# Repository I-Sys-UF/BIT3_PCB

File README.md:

# BIT3_PCB

KiCad 7.0.x にて設計

# BIT とは

**B**eginning **I**.Sys **T**racer のイニシャルで、新入生教育用のライントレーサの筐体です  
先代の BIT2 の設計を踏襲しつつ、マイコンを RP2040 搭載の秋月製 AE-RP2040 に置き換えました。ギアボックス等は流用できるようにしています

# 部品表

## 主要部品

| 部品番号 | 部品名 | 秋月 |
|:----|:----|:----|
| R1 - R5, R11 | 100 Ω | [125101](https://akizukidenshi.com/catalog/g/g125101/) |
| R6 - R10 | 4.7k Ω | [125273](https://akizukidenshi.com/catalog/g/g125273/) |
| R12 - R16 | 510 Ω | [125511](https://akizukidenshi.com/catalog/g/g125511/) |
| R17 - R21 | 1k Ω | [125102](https://akizukidenshi.com/catalog/g/g125102/) |
| C1 - C3 | 0.1 uF | [110147](https://akizukidenshi.com/catalog/g/g110147/) |
| D1 - D5 | 5mm LED | [113172](https://akizukidenshi.com/catalog/g/g113172/) |
| D6 | 1N4148 | [100941](https://akizukidenshi.com/catalog/g/g100941/) |
| U1 | AE-RP2040 | [117542](https://akizukidenshi.com/catalog/g/g117542/) |
| U2 - U6 | LBR-127HLD | [104500](https://akizukidenshi.com/catalog/g/g104500/) |
| U7 | MCP3008 | [109485](https://akizukidenshi.com/catalog/g/g109485/) |
| U7 | IC ソケット | [100007](https://akizukidenshi.com/catalog/g/g100007/) |
| U8 | AE-DRV8835 | [109848](https://akizukidenshi.com/catalog/g/g109848/) |
| U9 | NJM7805FA | [108678](https://akizukidenshi.com/catalog/g/g108678/) |
| Q1 | MOSFET | [107597](https://akizukidenshi.com/catalog/g/g107597/) |
| F1 | リセッタブルヒューズ | [112628](https://akizukidenshi.com/catalog/g/g112628/) |
| SW1 | 電源スイッチ | [100300](https://akizukidenshi.com/catalog/g/g100300/) |
| EXEC, MODE | タクタイルスイッチ | [103647](https://akizukidenshi.com/catalog/g/g103647/) |
| J1 | 2 列ピンヘッダ | [100080](https://akizukidenshi.com/catalog/g/g100080/) |
| J2 | バッテリ接続用ケーブル・コネクタ | 省略 |
| J3, U1 | 1 列ピンソケット | [105779](https://akizukidenshi.com/catalog/g/g105779/) |
| J5, J6 | 7 セグメント LED  | [110344](https://akizukidenshi.com/catalog/g/g110344/) |

## その他の部品

| 部品名 | 商品名 | リンク |
|:----|:----|:----|
| 前輪 | タミヤ　ボールキャスター | <https://tamiyashop.jp/shop/g/g70144> |
| 動力 | タミヤ　ダブルギヤボックス（左右独立4速タイプ） | <https://tamiyashop.jp/shop/g/g70168> |
| 後輪 | タミヤ　スリムタイヤセット | <https://tamiyashop.jp/shop/g/g70193> |
| XBee | XBee S2C ワイヤアンテナ型 | <https://www.switch-science.com/products/4089> |
| XBee 用変換基板 | XBeeエクスプローラ5Vマイコン用 | <https://www.switch-science.com/products/1166> |
| XBee 用 USB アダプタ | XBeeエクスプローラUSBドングル | <https://www.switch-science.com/products/1790> |

# 回路図

# 基板デザイン

# 更新履歴

- `v1.0`
  - 初回リリース
- `v1.1`
  - ADC にバッテリ電圧が直接入力される問題を修正
- `v1.2`
  - 接続されていない GND ベタが存在する問題を修正
- `v1.3`
  - モータ・ドライバに電源が供給されていない問題を修正
- `v1.4`
  - ADC IC MCP3008 にパスコンを追加
- `v1.5` 
  - 前輪と部品が微妙に干渉する問題を修正
- `v1.6`
  - 逆接防止ダイオードの追加、バッテリ入力の接続の変更、一部部品の変更（基板には影響なし）
- `v1.7`
  - フォトセンサを変更
- `v2.0`
  - XBee 接続用のコネクタを追加
- `v2.1`
  - BACK を EXEC に変更
- `v2.2`
  -  フォトセンサ駆動用トランジスタを変更
- `V2.3`
  - 7 セグメント LED モジュール用フットプリントを追加
  - センサ位置を微調整

# ライセンス

<br />この 作品 は <a rel="license" href="http://creativecommons.org/licenses/by-nc-nd/4.0/">クリエイティブ・コモンズ 表示 - 非営利 - 改変禁止 4.0 国際 ライセンス</a>の下に提供されています。

利用を希望される方は部の[公式 Twitter ](https://twitter.com/ISys_robocon)までご連絡ください

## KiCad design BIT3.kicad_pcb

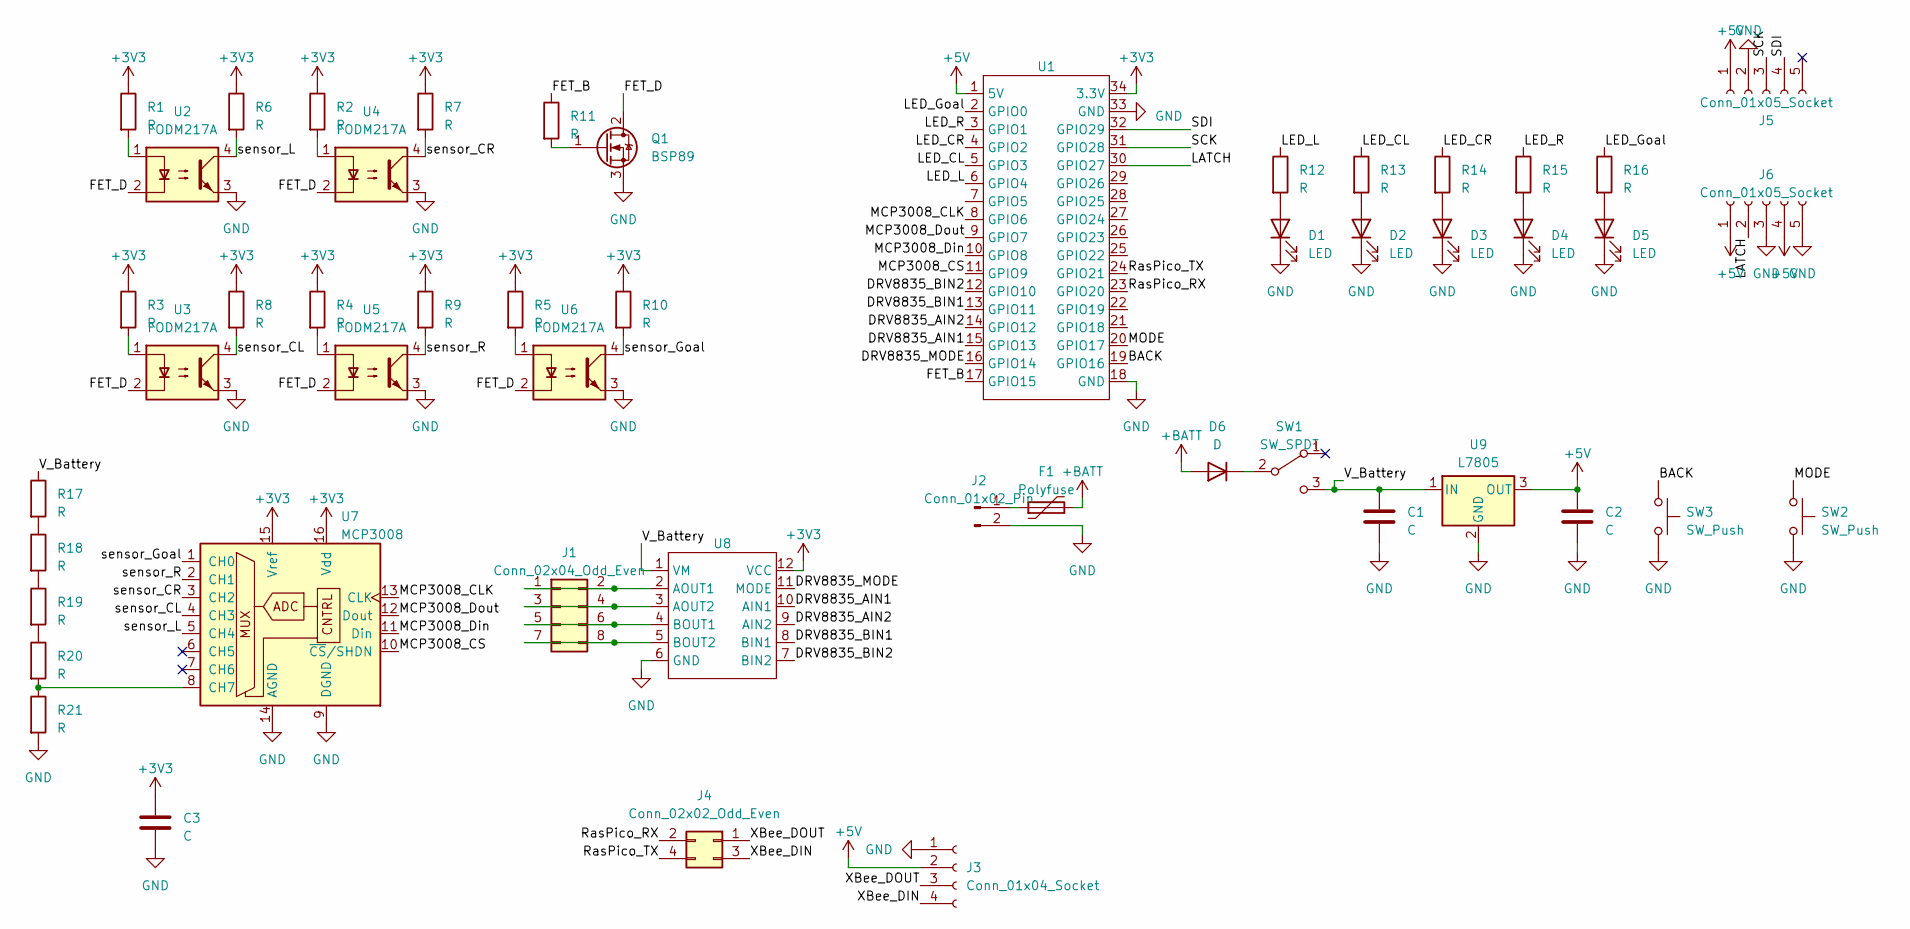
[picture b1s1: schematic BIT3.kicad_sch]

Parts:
C1, C2, C3: C; C_Disc_D4.7mm_W2.5mm_P5.00mm
D1, D2, D3, D4, D5: LED; LED_D5.0mm
D6: D; D_A-405_P7.62mm_Horizontal
F1: Polyfuse; Fuse_BelFuse_0ZRE0005FF_L8.3mm_W3.8mm
J1: Conn_02x04_Odd_Even; PinSocket_2x04_P2.54mm_Vertical
J2: Conn_01x02_Pin; PinSocket_1x02_P2.54mm_Vertical
J3: Conn_01x04_Socket; PinSocket_1x04_P2.54mm_Vertical
J4: Conn_02x02_Odd_Even; PinSocket_2x02_P2.54mm_Vertical
J5, J6: Conn_01x05_Socket; PinSocket_1x05_P2.54mm_Vertical
Q1: BSP89; TO-220-3_Vertical
R1, R2, R3, R4, R5, R6, R7, R8, R9, R10, R11, R12, R13, R14, R15, R16, R17, R18, R19, R20, R21: R; R_Axial_DIN0204_L3.6mm_D1.6mm_P7.62mm_Horizontal
SW1: SW_SPDT; SW_Slide_1P2T_CK_OS102011MS2Q
SW2, SW3: SW_Push; SW_PUSH_6mm
U1: AE-RP2040
U2, U3, U4, U5, U6: FODM217A; LBR-127HLD
U7: MCP3008; DIP-16_W7.62mm
U8: AE-DRV8835
U9: L7805; TO-220-3_Vertical

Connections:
+3V3: C3.1, R1.1, R2.1, R3.1, R4.1, R5.1, R6.1, R7.1, R8.1, R9.1, R10.1, U1.34 (3.3V), U7.15 (Vref), U7.16 (Vdd), U8.12 (VCC)
+5V: C2.1, J3.2, J5.1, J6.1, J6.4, U1.1 (5V), U9.3 (OUT)
+BATT: D6.2 (A), F1.2
/BACK: SW3.1, U1.19 (GPIO16)
/DRV8835_AIN1: U1.15 (GPIO13), U8.10 (AIN1)
/DRV8835_AIN2: U1.14 (GPIO12), U8.9 (AIN2)
/DRV8835_BIN1: U1.13 (GPIO11), U8.8 (BIN1)
/DRV8835_BIN2: U1.12 (GPIO10), U8.7 (BIN2)
/DRV8835_MODE: U1.16 (GPIO14), U8.11 (MODE)
/FET_B: R11.1, U1.17 (GPIO15)
/FET_D: Q1.2 (D), U2.2, U3.2, U4.2, U5.2, U6.2
/LATCH: J6.2, U1.30 (GPIO27)
/LED_CL: R13.1, U1.5 (GPIO3)
/LED_CR: R14.1, U1.4 (GPIO2)
/LED_Goal: R16.1, U1.2 (GPIO0)
/LED_L: R12.1, U1.6 (GPIO4)
/LED_R: R15.1, U1.3 (GPIO1)
/MCP3008_CLK: U1.8 (GPIO6), U7.13 (CLK)
/MCP3008_CS: U1.11 (GPIO9), U7.10 (~CS/SHDN)
/MCP3008_Din: U1.10 (GPIO8), U7.11 (Din)
/MCP3008_Dout: U1.9 (GPIO7), U7.12 (Dout)
/MODE: SW2.1, U1.20 (GPIO17)
/RasPico_RX: J4.2, U1.23 (GPIO20)
/RasPico_TX: J4.4, U1.24 (GPIO21)
/SCK: J5.3, U1.31 (GPIO28)
/SDI: J5.4, U1.32 (GPIO29)
/V_Battery: C1.1, R17.1, SW1.3 (C), U8.1 (VM), U9.1 (IN)
/XBee_DIN: J3.4, J4.3
/XBee_DOUT: J3.3, J4.1
/sensor_CL: R8.2, U3.4, U7.4 (CH3)
/sensor_CR: R7.2, U4.4, U7.3 (CH2)
/sensor_Goal: R10.2, U6.4, U7.1 (CH0)
/sensor_L: R6.2, U2.4, U7.5 (CH4)
/sensor_R: R9.2, U5.4, U7.2 (CH1)
GND: C1.2, C2.2, C3.2, D1.1 (K), D2.1 (K), D3.1 (K), D4.1 (K), D5.1 (K), J2.2, J3.1, J5.2, J6.3, J6.5, Q1.3 (S), R21.2, SW2.2, SW3.2, U1.18 (GND), U1.33 (GND), U2.3, U3.3, U4.3, U5.3, U6.3, U7.9 (DGND), U7.14 (AGND), U8.6 (GND), U9.2 (GND)
unnamed: D1.2 (A), R12.2
unnamed: D2.2 (A), R13.2
unnamed: D3.2 (A), R14.2
unnamed: D4.2 (A), R15.2
unnamed: D5.2 (A), R16.2
unnamed: D6.1 (K), SW1.2 (B)
unnamed: J1.1, J1.2, U8.2 (AOUT1)
unnamed: J1.3, J1.4, U8.3 (AOUT2)
unnamed: J1.5, J1.6, U8.4 (BOUT1)
unnamed: J1.7, J1.8, U8.5 (BOUT2)
unnamed: F1.1, J2.1
unnamed: Q1.1 (G), R11.2
unnamed: R1.2, U2.1
unnamed: R2.2, U4.1
unnamed: R3.2, U3.1
unnamed: R4.2, U5.1
unnamed: R5.2, U6.1
unnamed: R17.2, R18.1
unnamed: R18.2, R19.1
unnamed: R19.2, R20.1
unnamed: R20.2, R21.1, U7.8 (CH7)

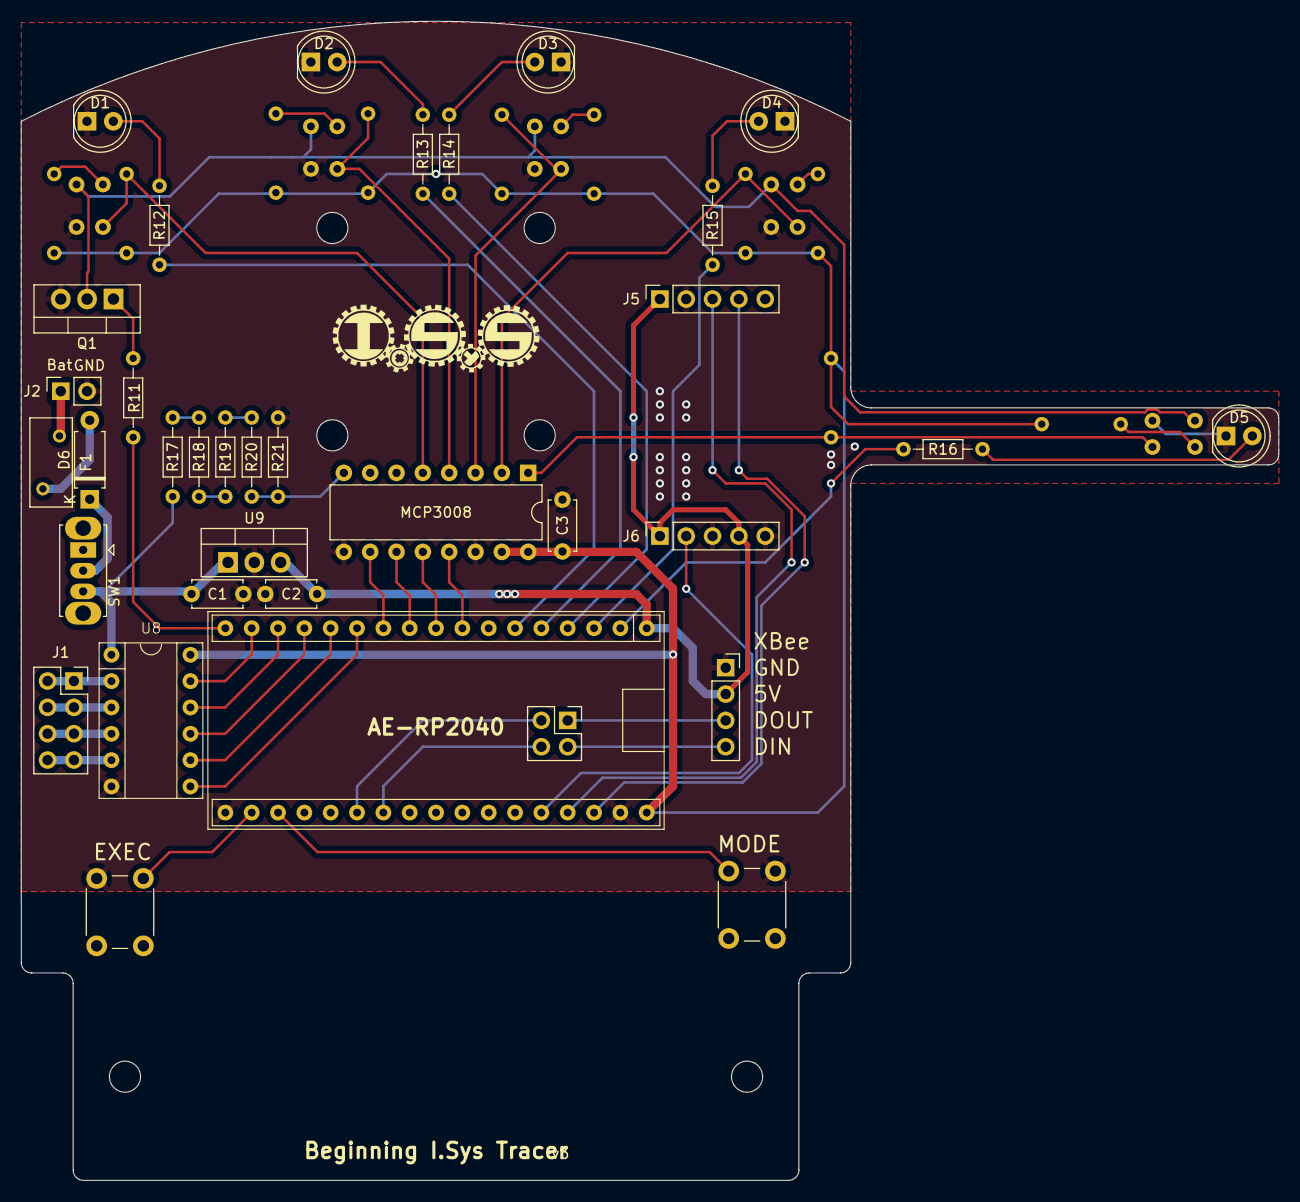
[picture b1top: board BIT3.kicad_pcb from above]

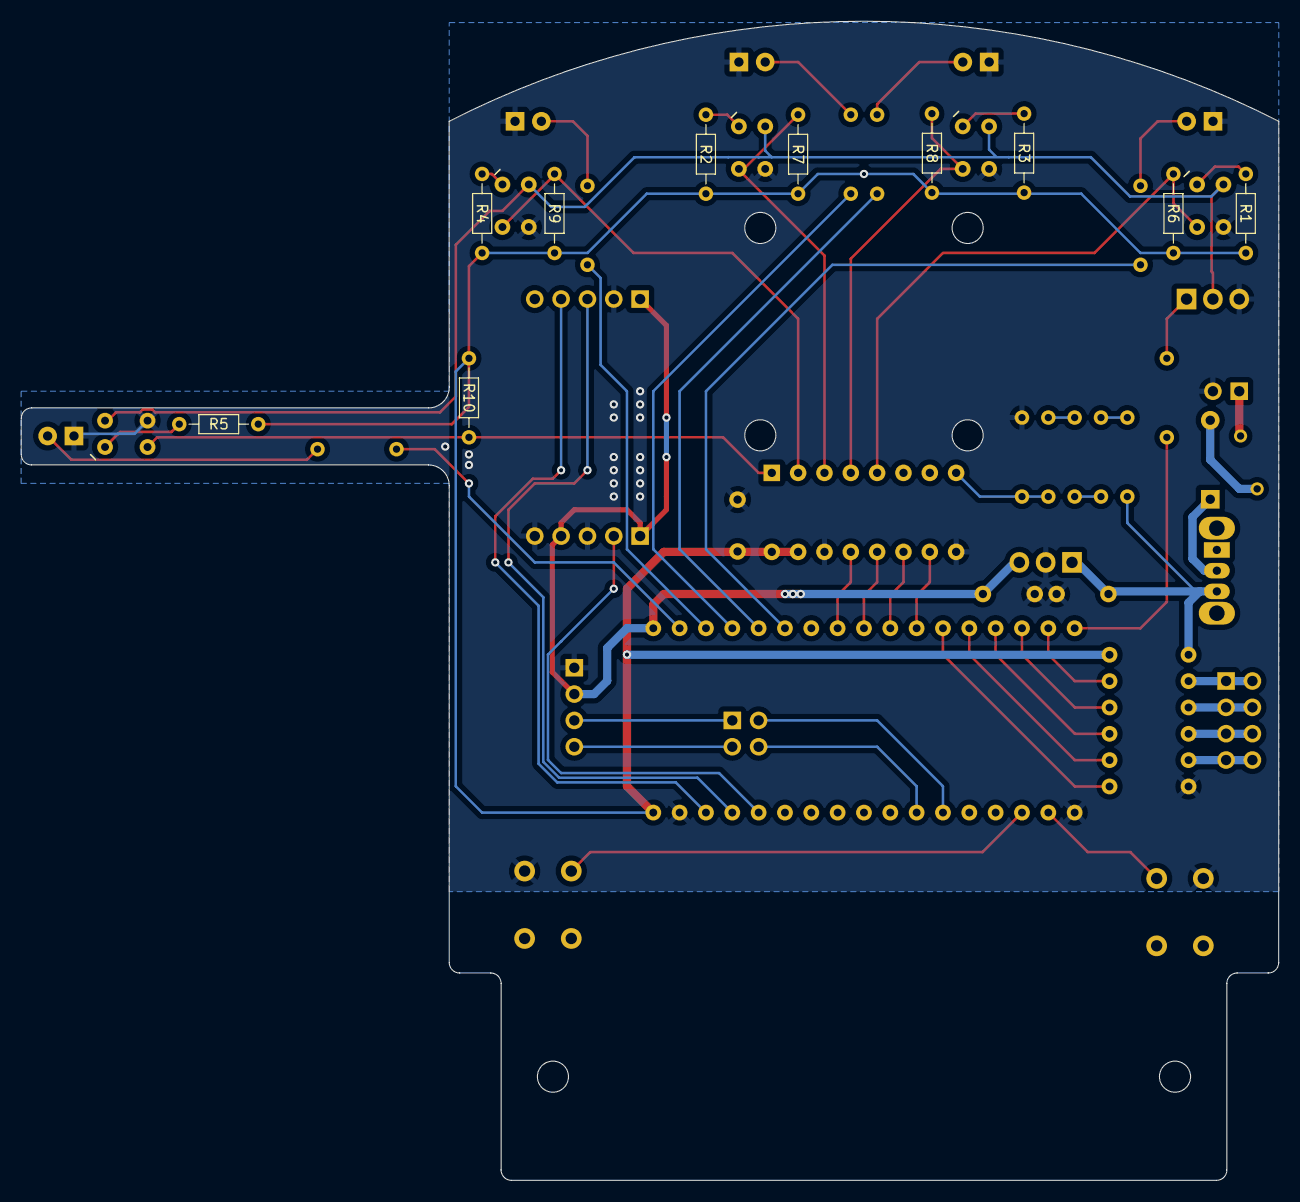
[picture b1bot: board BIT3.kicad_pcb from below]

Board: 2 copper layers, 121.3 x 111.8 mm, 50 parts (15 on the bottom side), 56 nets.

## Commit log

2023-06-04 Update PCB Design
2023-06-04 部品表を追加
2023-06-04 Update PCB Design
    - remove `SW2` and `SW3` silkscreen
    - add silkscreen print
    - `SW2` as `MODE`, `SW3` as `BACK`
2023-06-05 Update PCB Design
    add GND vias
2023-06-05 更新履歴を追加
2023-06-05 Update PCB Design
    fix Power Supply
2023-06-08 add readme
2023-06-08 edit license
2023-06-09 add PCB Design
2023-06-09 Rename BIT3.svg to img/BIT3.svg
2023-06-09 画像ファイルパス変更に合わせ画像リンクを更新
2023-06-09 基板更新
    MCP3008 にパスコンを追加
2023-06-09 Update image
2023-06-29 逆説防止 D を追加, バッテリ電圧監視 ADC の配置を変更
2023-06-29 部品表更新
2023-06-29 フォトセンサを変更
2023-06-30 XBee を接続できるように変更
2023-06-30 更新履歴を追記
2023-07-02 モータの電源を BATT から 5V に変更
2023-07-04 モータ電源を BATT に戻した
2023-07-04 画像更新
2023-07-18 BACK -> EXEC
2023-07-18 部品表追記
2023-08-02 フォトリフレクタを変更
2023-11-09 R1 - R5 の抵抗値を変更
2024-01-05 Tr を置き換え
2024-02-05 赤外線 LED 用トランジスタを変更
2024-04-10 MOSFET
2024-04-10 Tr 置き換え，部品表更新
2024-04-27 7 セグメント LED 用フットプリントを追加
2024-06-11 センサ位置修正
2024-06-11 部品変更
2024-06-21 センサ位置調整
2024-06-21 更新履歴追記
2024-06-28 update parts

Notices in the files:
README.md:
CC BY-NC-ND 4.0
